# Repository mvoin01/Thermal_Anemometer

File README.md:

# Thermal_Anemometer
Thermal_Anemometer ELEC70101

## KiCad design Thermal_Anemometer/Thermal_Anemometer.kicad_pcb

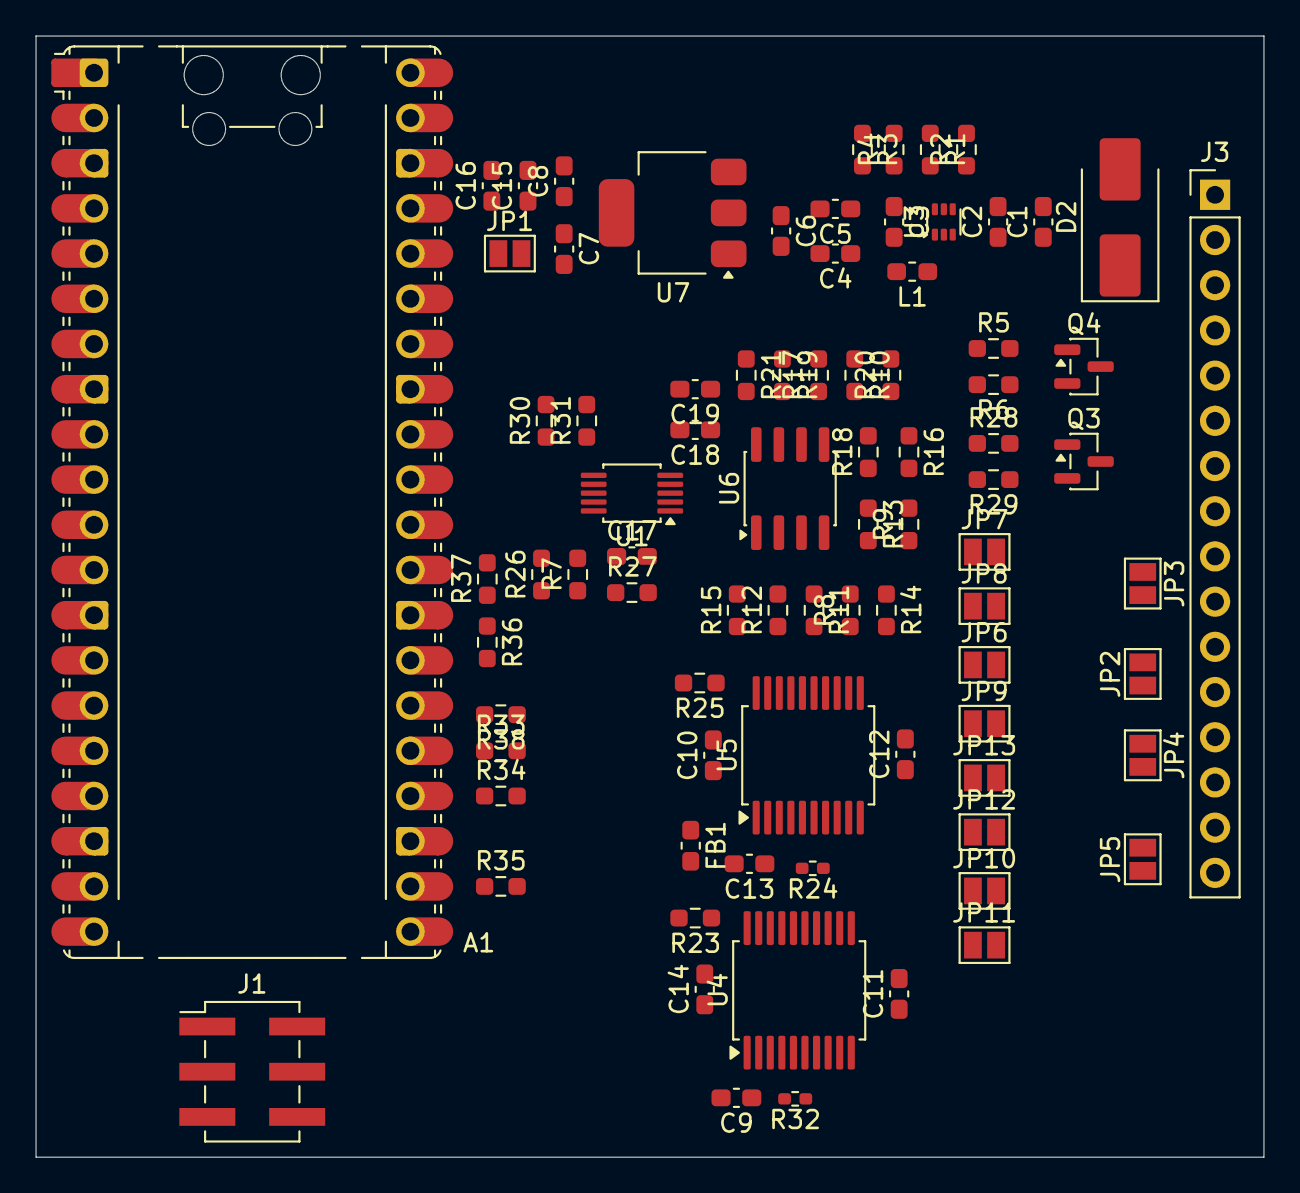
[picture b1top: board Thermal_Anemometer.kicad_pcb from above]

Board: 2 copper layers, 69.0 x 63.0 mm, 83 parts (0 on the bottom side), 55 nets, no tracks yet.

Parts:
A1: RaspberryPi_Pico; RaspberryPi_Pico_Common_Unspecified
C1, C6, C15, C18: 10uF; C_0603_1608Metric_Pad1.08x0.95mm_HandSolder
C2, C3, C8, C9, C10, C13, C14, C16, C17, C19: 100nF; C_0603_1608Metric_Pad1.08x0.95mm_HandSolder
C4, C5, C7: 22uF; C_0603_1608Metric_Pad1.08x0.95mm_HandSolder
C11, C12: 10nF; C_0603_1608Metric_Pad1.08x0.95mm_HandSolder
D2: TVS 15V; D_SMB_Handsoldering
FB1: FerriteBead; L_0603_1608Metric_Pad1.05x0.95mm_HandSolder
J1: Conn_02x03_Odd_Even; PinHeader_2x03_P2.54mm_Vertical_SMD
J3: Conn_01x16_Pin; PinHeader_1x16_P2.54mm_Vertical
JP1, JP2, JP3, JP4, JP5, JP6, JP7, JP8, JP9, JP10, JP11, JP12, JP13: Jumper_2_Open; SolderJumper-2_P1.3mm_Open_Pad1.0x1.5mm
L1: 33uH; L_0603_1608Metric_Pad1.05x0.95mm_HandSolder
Q3, Q4: DMN3404L; SOT-23
R1: 33k; R_0603_1608Metric_Pad0.98x0.95mm_HandSolder
R2, R4, R7, R14, R15, R20, R21, R26, R27, R35, R36, R37, R38: 10k; R_0603_1608Metric_Pad0.98x0.95mm_HandSolder
R3: 64.9k; R_0603_1608Metric_Pad0.98x0.95mm_HandSolder
R5, R28: 100; R_0603_1608Metric_Pad0.98x0.95mm_HandSolder
R6, R29, R30, R31: 100k; R_0603_1608Metric_Pad0.98x0.95mm_HandSolder
R8, R9, R10, R11, R12, R13, R16, R17, R18, R19: 1k; R_0603_1608Metric_Pad0.98x0.95mm_HandSolder
R23, R25, R33, R34: 22; R_0603_1608Metric_Pad0.98x0.95mm_HandSolder
R24, R32: 2.2k; R_0402_1005Metric_Pad0.72x0.64mm_HandSolder
U1: ADS1115IDGS; TSSOP-10_3x3mm_P0.5mm
U3: AP62300Z6; SOT-563
U4, U5: MAX31865xAP; SSOP-20_5.3x7.2mm_P0.65mm
U6: LM358; SOIC-8_3.9x4.9mm_P1.27mm
U7: NCP1117-3.3_SOT223; SOT-223-3_TabPin2

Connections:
+3.3V: C7.1, C8.1, C10.1, C14.1, C15.1, C16.1, C17.1, FB1.1, JP1.2 (B), R7.1, R8.1, R9.1, R10.1, R16.1, R26.1, R27.1, R35.1, R36.1, R37.1, R38.1, U1.8 (VDD), U4.2 (DVDD), U5.2 (DVDD), U7.2 (VO)
+3.3VA: C9.1, C13.1, FB1.2, U4.3 (VDD), U5.3 (VDD)
+6V: C4.1, C5.1, C6.1, C18.1, C19.1, J3.3, J3.6, L1.2, R3.1, U6.8 (V+), U7.3 (VI)
+12V: C1.1, C2.1, D2.1 (K), J3.2, R1.1, U3.1 (VIN)
/ADC/ADC_RDY/ALERT: R27.2, U1.2 (ALERT/RDY)
/ADC/I2C_SCL: A1.2 (GPIO1), R7.2, U1.10 (SCL)
/ADC/I2C_SDA: A1.1 (GPIO0), R26.2, U1.9 (SDA)
/A_OUT1: R15.2, U1.4 (AIN0), U6.1
/A_OUT2: R21.2, U1.5 (AIN1), U6.7
/MAX31865/REFIN1+: R32.2, U4.4 (BIAS), U4.5 (REFIN+)
/MAX31865/REFIN1-: R32.1, U4.6 (REFIN-), U4.7 (ISENSOR)
/MAX31865/REFIN2+: R24.2, U5.4 (BIAS), U5.5 (REFIN+)
/MAX31865/REFIN2-: R24.1, U5.6 (REFIN-), U5.7 (ISENSOR)
/PT1000_1+: C11.1, J3.10, JP3.2 (B), JP6.2 (B), JP10.1 (A), JP10.2 (B), U4.10 (RTDIN+)
/PT1000_1-: C11.2, J3.11, JP2.2 (B), JP7.2 (B), JP11.1 (A), JP11.2 (B), U4.11 (RTDIN-)
/PT1000_2+: C12.1, J3.14, JP4.2 (B), JP8.2 (B), JP12.1 (A), JP12.2 (B), U5.10 (RTDIN+)
/PT1000_2-: C12.2, J3.15, JP5.2 (B), JP9.2 (B), JP13.1 (A), JP13.2 (B), U5.11 (RTDIN-)
/PT1000_4Wire_1+: J3.9, JP3.1 (A), U4.8 (FORCE+)
/PT1000_4Wire_1-: J3.12, JP2.1 (A), U4.12 (FORCE-)
/PT1000_4Wire_2+: J3.13, JP4.1 (A), U5.8 (FORCE+)
/PT1000_4Wire_2-: J3.16, JP5.1 (A), U5.12 (FORCE-)
/RP_Pico/3V3_Pico: A1.36 (3V3), J1.4, JP1.1 (A)
/RP_Pico/RUN: A1.30 (RUN), J1.5
/SPI_CLK: R34.2, U4.15 (SCLK), U5.15 (SCLK)
/SPI_MISO: A1.21 (GPIO16), R23.2, R25.2
/SPI_MOSI: R33.2, U4.14 (SDI), U5.14 (SDI)
/SPI_nDRDY1: A1.26 (GPIO20), R38.2, U4.1 (~DRDY)
/SPI_nDRDY2: A1.27 (GPIO21), R36.2, U5.1 (~DRDY)
/Wheatstone_Bridge/PT1000_1+W: JP6.1 (A), R9.2, R13.1
/Wheatstone_Bridge/PT1000_2+W: JP8.1 (A), R16.2, R18.1
/nCS1: A1.22 (GPIO17), R35.2, U4.16 (~CS)
/nCS2: A1.29 (GPIO22), R37.2, U5.16 (~CS)
/uHeater1-: J3.4, Q4.3 (D)
/uHeater1_EN: A1.4 (GPIO2), R5.1
/uHeater2-: J3.7, Q3.3 (D)
/uHeater2_EN: A1.5 (GPIO3), R28.1
GND: A1.3 (GND), A1.8 (GND), A1.13 (GND), A1.18 (GND), A1.23 (GND), A1.28 (GND), A1.38 (GND), C1.2, C2.2, C4.2, C5.2, C6.2, C7.2, C8.2, C9.2, C10.2, C13.2, C14.2, C15.2, C16.2, C17.2, C18.2, C19.2, D2.2 (A), J1.2, J1.6, J3.1, JP7.1 (A), JP9.1 (A), Q3.2 (S), Q4.2 (S), R2.2, R4.2, R6.2, R11.2, R14.2, R17.2, R20.2, R29.2, R30.2, R31.2, U1.1 (ADDR), U1.3 (GND), U3.3 (GND), U4.9 (FORCE2), U4.13 (GND), U4.18 (DGND), U4.19 (GND), U5.9 (FORCE2), U5.13 (GND), U5.18 (DGND), U5.19 (GND), U6.4 (V-), U7.1 (GND)
unnamed: A1.24 (GPIO18), R34.1
unnamed: A1.25 (GPIO19), R33.1
unnamed: Q3.1 (G), R28.2, R29.1
unnamed: Q4.1 (G), R5.2, R6.1
unnamed: R10.2, R17.1, R19.1
unnamed: R8.2, R11.1, R12.1
unnamed: R31.1, U1.6 (AIN2)
unnamed: R30.1, U1.7 (AIN3)
unnamed: C3.1, U3.4 (BST)
unnamed: R1.2, R2.1, U3.5 (EN)
unnamed: R3.2, R4.1, U3.6 (FB)
unnamed: C3.2, L1.1, U3.2 (SW)
unnamed: R23.1, U4.17 (SDO)
unnamed: R25.1, U5.17 (SDO)
unnamed: R13.2, R14.1, U6.3 (+)
unnamed: R12.2, R15.1, U6.2 (-)
unnamed: R18.2, R20.1, U6.5 (+)
unnamed: R19.2, R21.1, U6.6 (-)
